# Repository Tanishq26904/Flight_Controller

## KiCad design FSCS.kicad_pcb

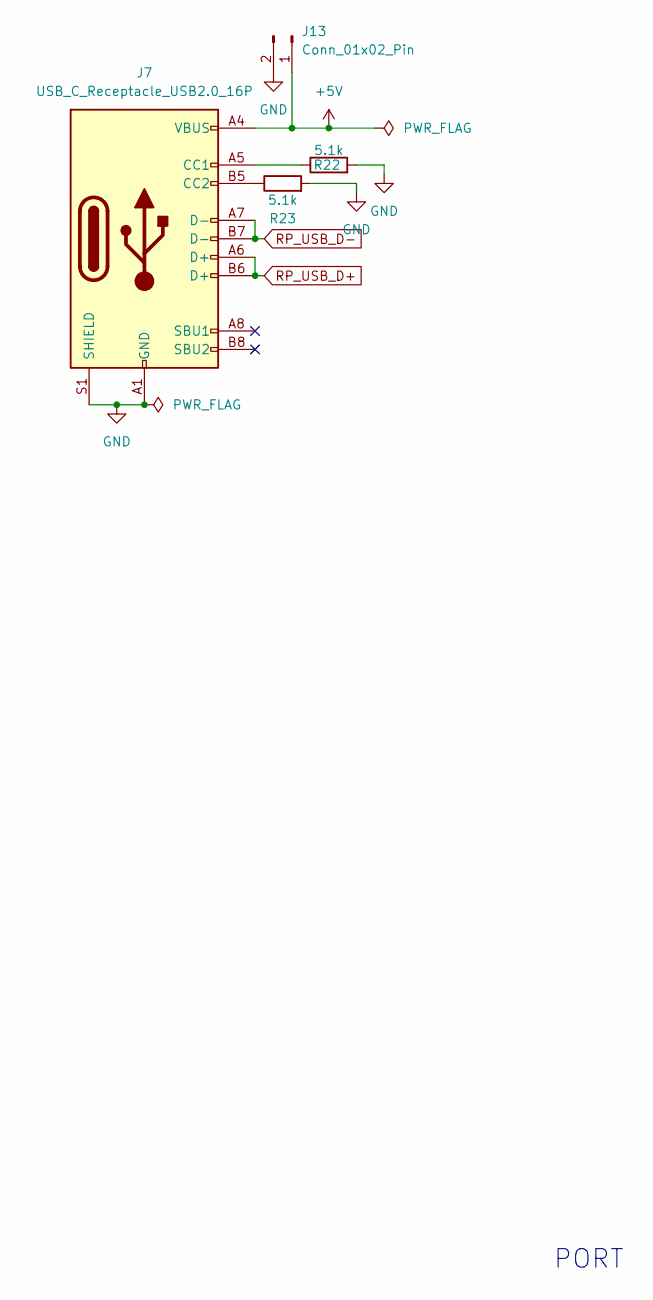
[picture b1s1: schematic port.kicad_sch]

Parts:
J7: USB_C_Receptacle_USB2.0_16P; USB_C_Receptacle_G-Switch_GT-USB-7010ASV
J13: Conn_01x02_Pin; PinHeader_1x02_P2.54mm_Horizontal
R22, R23: 5.1k; R_0603_1608Metric_Pad0.98x0.95mm_HandSolder

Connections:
+5V: J7.A4 (VBUS), J7.A9 (VBUS), J7.B4 (VBUS), J7.B9 (VBUS), J13.1; also elsewhere on the board
GND: J7.A1 (GND), J7.A12 (GND), J7.B1 (GND), J7.B12 (GND), J7.S1 (SHIELD), J13.2, R22.2, R23.2; also elsewhere on the board
unnamed: J7.A5 (CC1), R22.1
unnamed: J7.B5 (CC2), R23.1
RP_USB_D+: J7.A6 (D+), J7.B6 (D+); also elsewhere on the board
RP_USB_D-: J7.A7 (D-), J7.B7 (D-); also elsewhere on the board

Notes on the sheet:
PORT

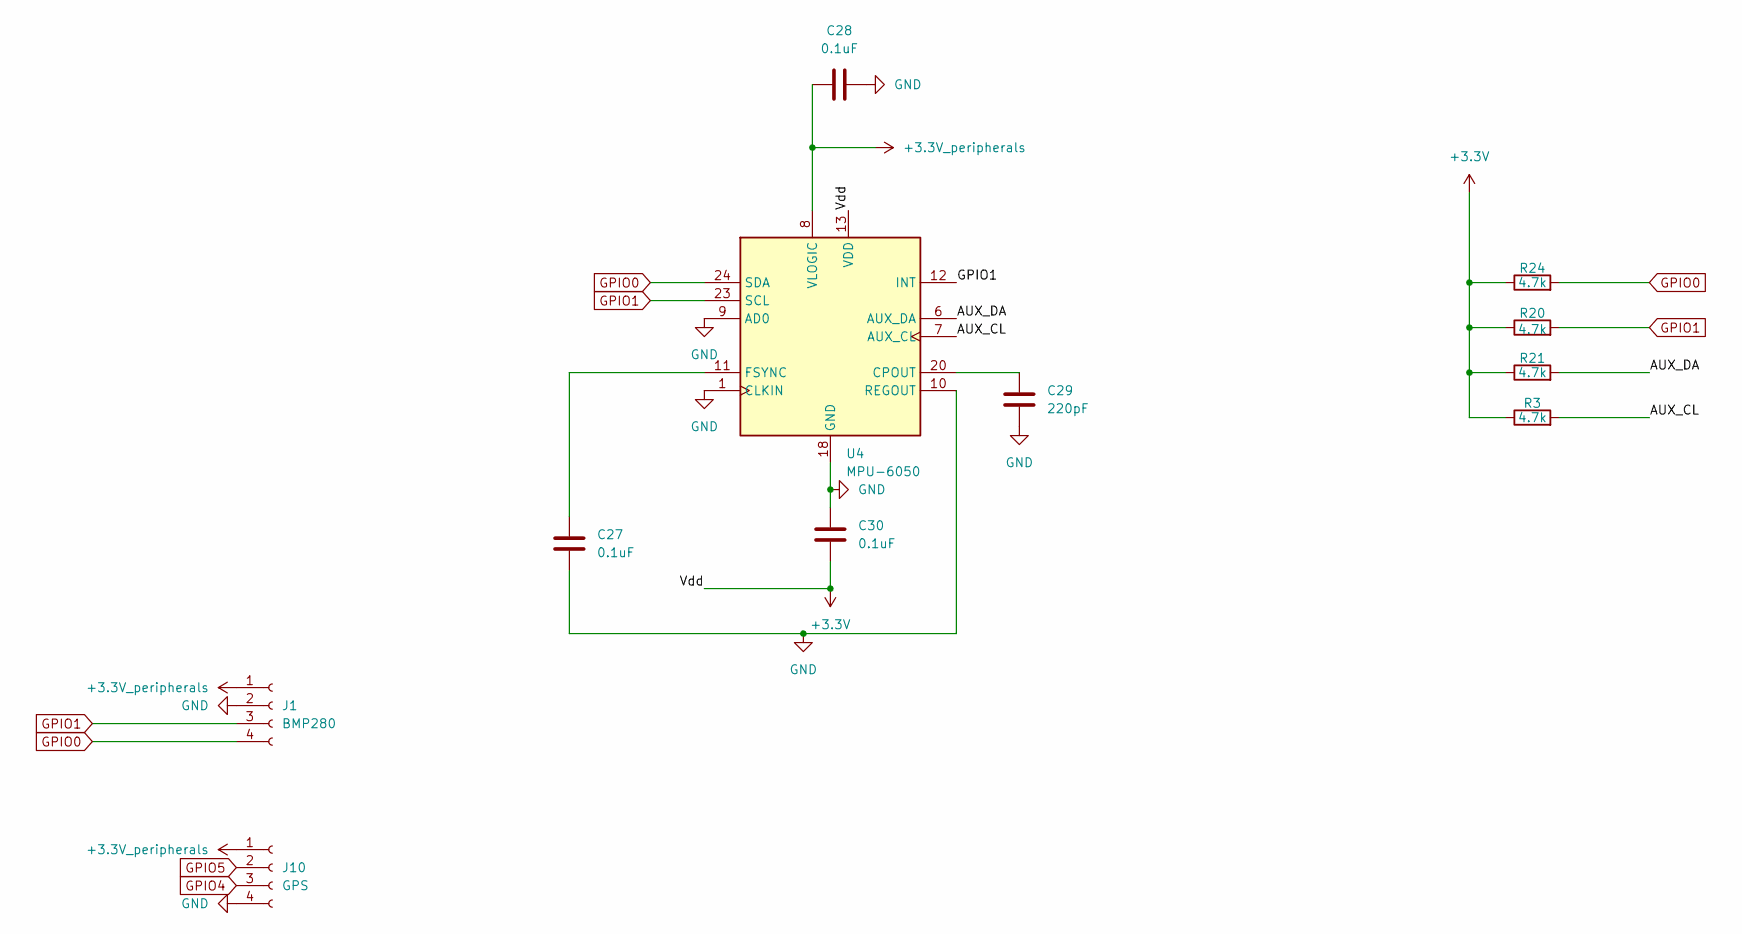
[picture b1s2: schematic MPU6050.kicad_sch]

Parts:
C27, C28, C30: 0.1uF; C_0603_1608Metric_Pad1.08x0.95mm_HandSolder
C29: 220pF; C_0603_1608Metric_Pad1.08x0.95mm_HandSolder
J1: BMP280; PinSocket_1x04_P2.54mm_Vertical
J10: GPS; PinSocket_1x04_P2.54mm_Vertical
R3, R20, R21, R24: 4.7k; R_0603_1608Metric_Pad0.98x0.95mm_HandSolder
U4: MPU-6050; InvenSense_QFN-24_4x4mm_P0.5mm

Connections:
/MPU6050/AUX_CL: R3.2, U4.7 (AUX_CL)
/MPU6050/AUX_DA: R21.2, U4.6 (AUX_DA)
GND: C27.2, C28.2, C29.2, C30.1, J1.2, J10.4, U4.1 (CLKIN), U4.9 (AD0), U4.10 (REGOUT), U4.18 (GND); also elsewhere on the board
GPIO0: J1.4, R24.2, U4.24 (SDA); also elsewhere on the board
GPIO1: J1.3, R20.2, U4.12 (INT), U4.23 (SCL); also elsewhere on the board
GPIO4: J10.3; also elsewhere on the board
GPIO5: J10.2; also elsewhere on the board
unnamed: C29.1, U4.20 (CPOUT)
unnamed: C27.1, U4.11 (FSYNC)

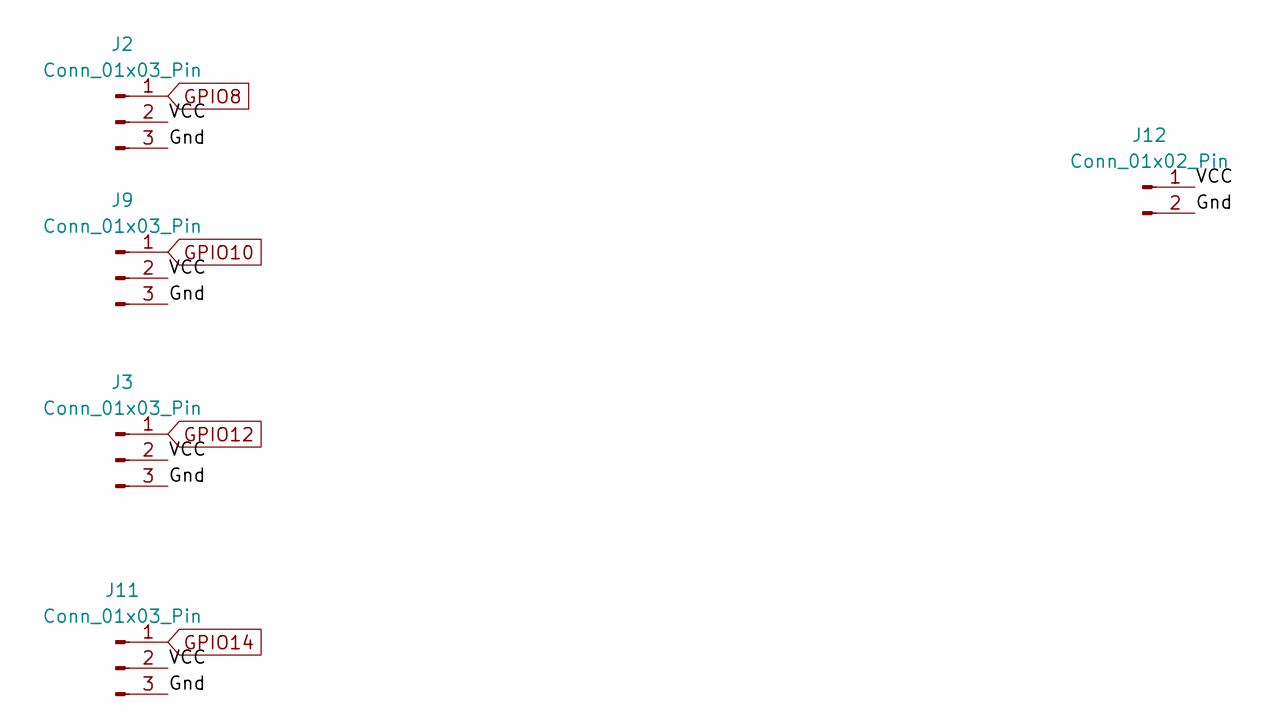
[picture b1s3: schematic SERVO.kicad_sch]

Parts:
J2, J3, J9, J11: Conn_01x03_Pin; PinHeader_1x03_P2.54mm_Vertical
J12: Conn_01x02_Pin; PinHeader_1x02_P2.54mm_Horizontal

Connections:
/SERVO/Gnd: J2.3, J3.3, J9.3, J11.3, J12.2
/SERVO/VCC: J2.2, J3.2, J9.2, J11.2, J12.1
GPIO8: J2.1; also elsewhere on the board
GPIO10: J9.1; also elsewhere on the board
GPIO12: J3.1; also elsewhere on the board
GPIO14: J11.1; also elsewhere on the board

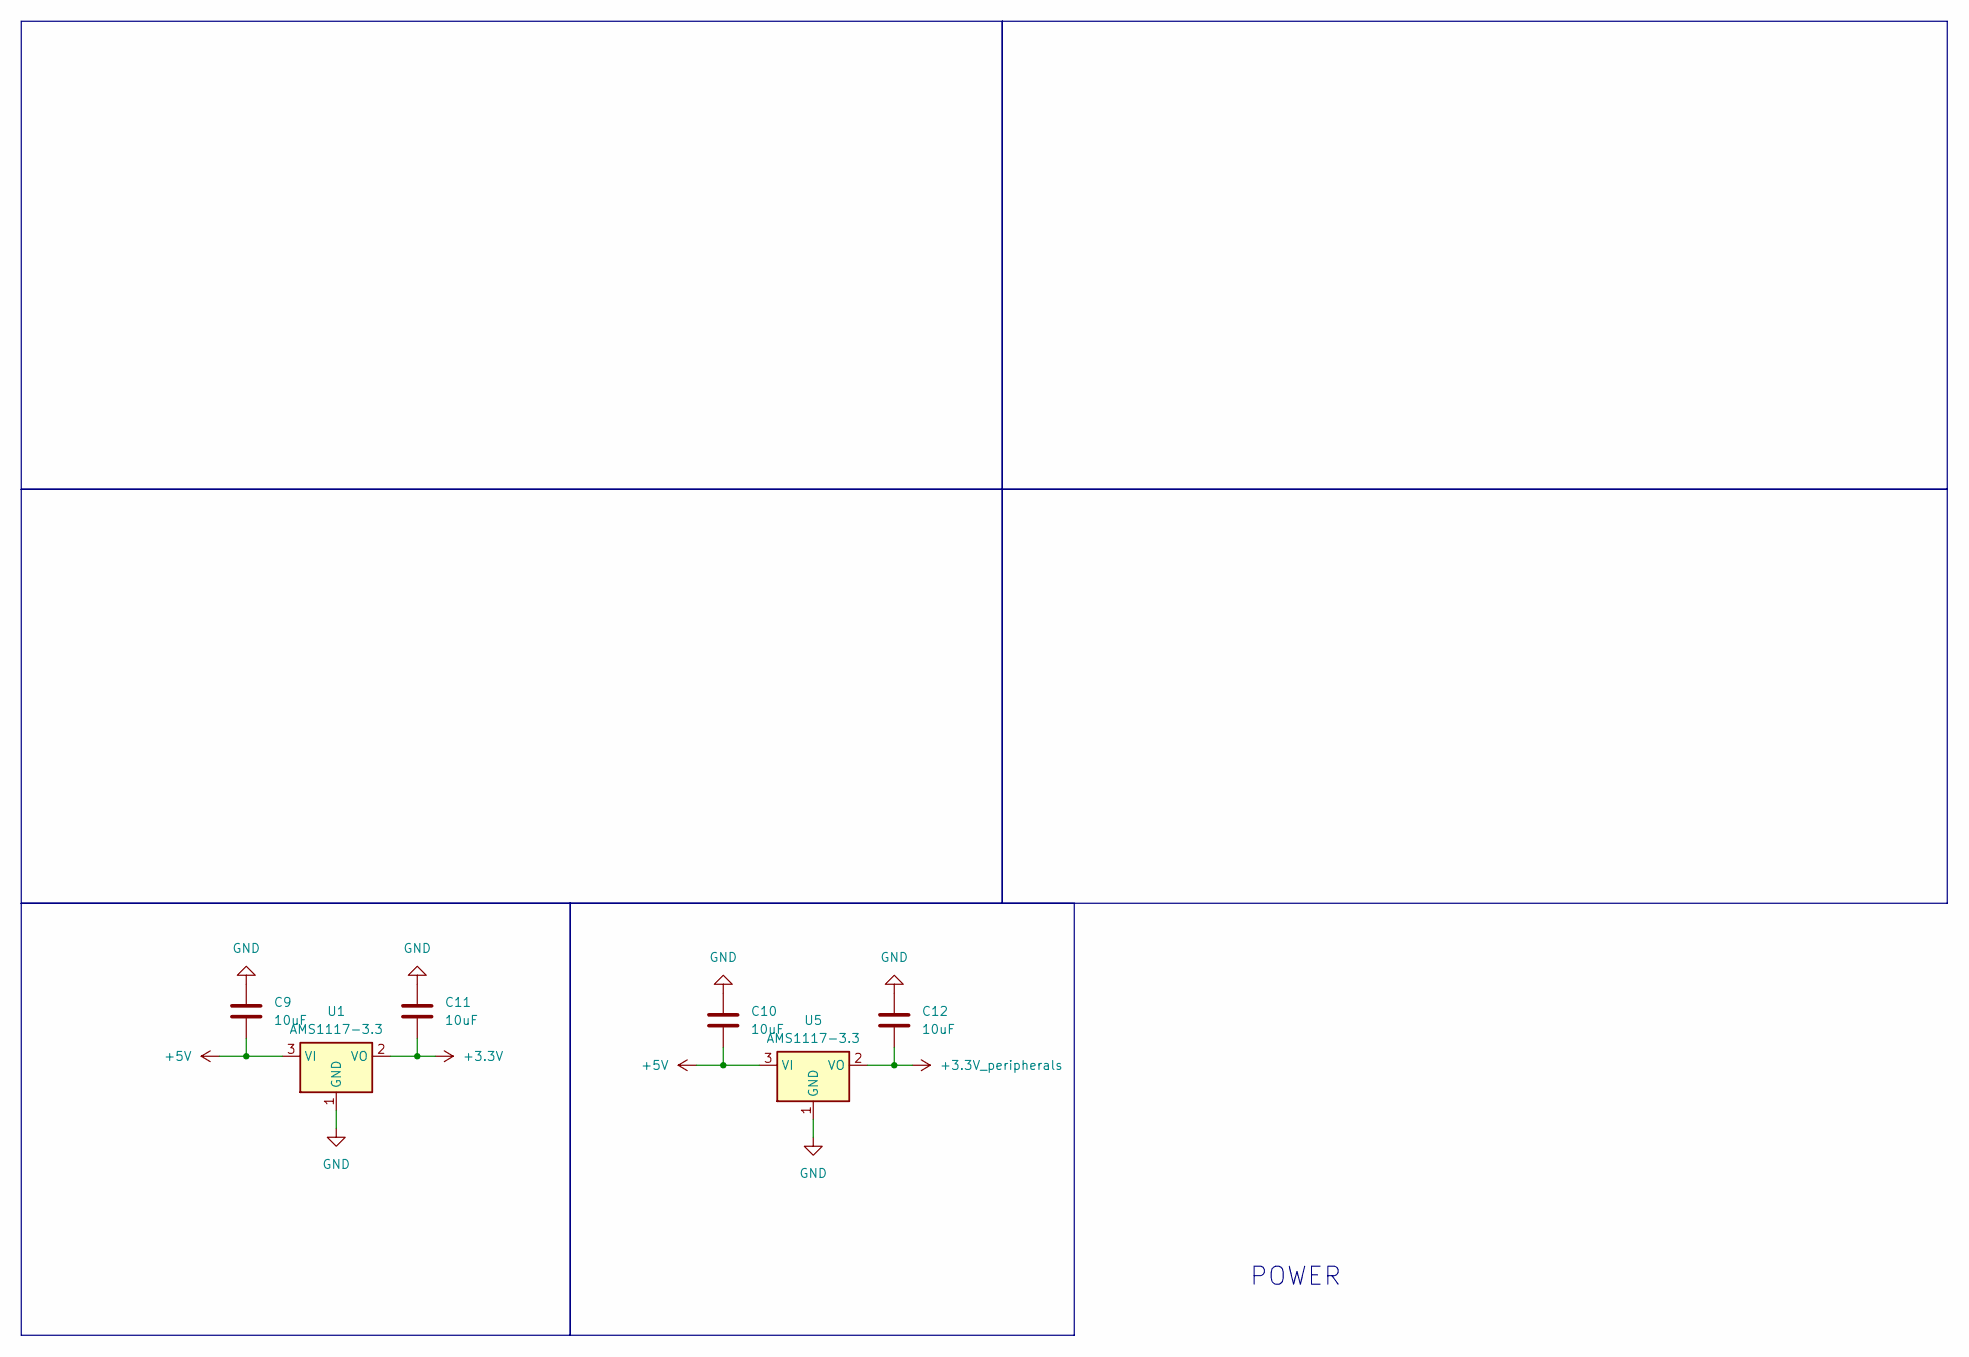
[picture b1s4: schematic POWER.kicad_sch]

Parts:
C9, C10, C11, C12: 10uF; C_0603_1608Metric_Pad1.08x0.95mm_HandSolder
U1, U5: AMS1117-3.3; SOT-223-3_TabPin2

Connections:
+5V: C9.2, C10.2, U1.3 (VI), U5.3 (VI); also elsewhere on the board
GND: C9.1, C10.1, C11.1, C12.1, U1.1 (GND), U5.1 (GND); also elsewhere on the board
unnamed: C12.2, U5.2 (VO)

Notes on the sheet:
POWER

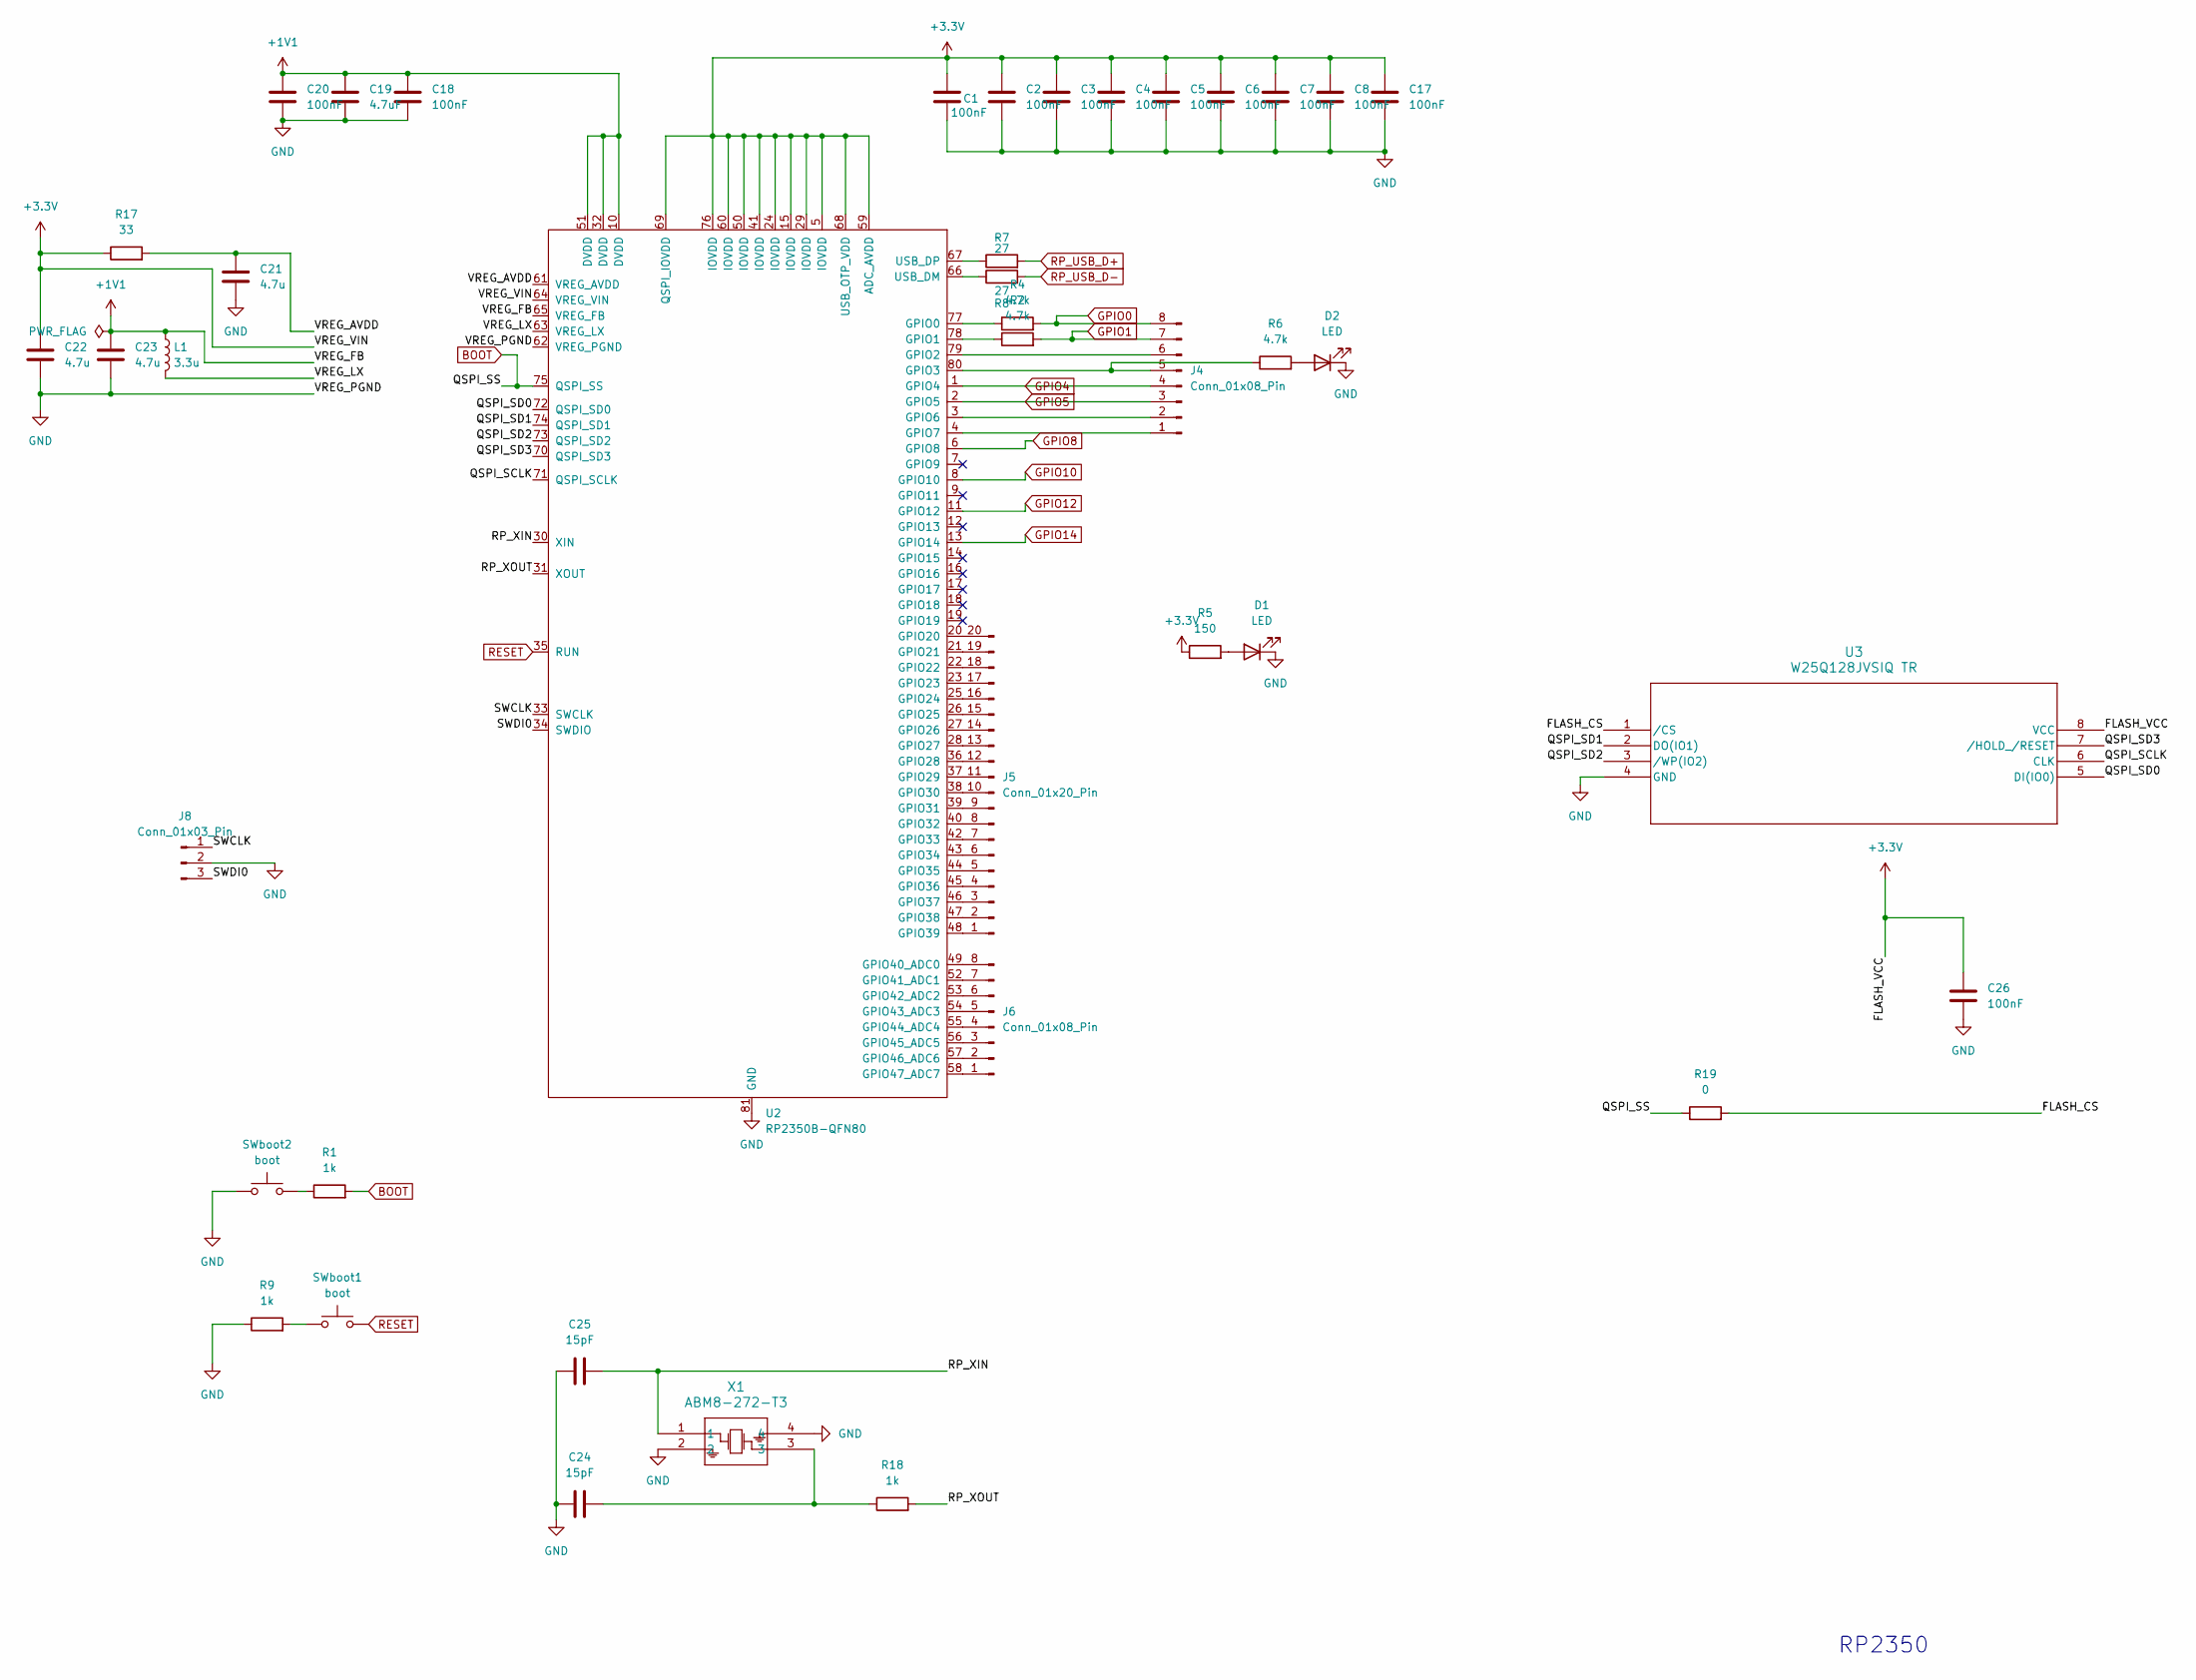
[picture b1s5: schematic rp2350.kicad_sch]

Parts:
C1, C2, C3, C4, C5, C6, C7, C8, C17, C18, C20, C26: 100nF; C_0603_1608Metric_Pad1.08x0.95mm_HandSolder
C19: 4.7uF; C_0603_1608Metric_Pad1.08x0.95mm_HandSolder
C21, C22, C23: 4.7u; C_0603_1608Metric_Pad1.08x0.95mm_HandSolder
C24, C25: 15pF; C_0603_1608Metric_Pad1.08x0.95mm_HandSolder
D1, D2: LED; LED_1206_3216Metric_Pad1.42x1.75mm_HandSolder
J4, J6: Conn_01x08_Pin; PinHeader_1x08_P2.54mm_Vertical
J5: Conn_01x20_Pin; PinHeader_1x20_P2.54mm_Vertical
J8: Conn_01x03_Pin; PinHeader_1x03_P2.54mm_Vertical
L1: 3.3u; L_1210_3225Metric_Pad1.42x2.65mm_HandSolder
R1, R9, R18: 1k; R_0603_1608Metric_Pad0.98x0.95mm_HandSolder
R2, R4, R6: 4.7k; R_0603_1608Metric_Pad0.98x0.95mm_HandSolder
R5: 150; R_0603_1608Metric_Pad0.98x0.95mm_HandSolder
R7, R8: 27; R_0603_1608Metric_Pad0.98x0.95mm_HandSolder
R17: 33; R_0603_1608Metric_Pad0.98x0.95mm_HandSolder
R19: 0; R_0603_1608Metric_Pad0.98x0.95mm_HandSolder
SWboot1, SWboot2: boot; SW_SPST_TL3342
U2: RP2350B-QFN80; QFN-80-1EP_10x10mm_P0.4mm_EP3.4x3.4mm
U3: W25Q128JVSIQ TR; SOIC_208MIL_WIN
X1: ABM8-272-T3; ABM8-272-T3_ABR

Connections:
+1V1: C18.1, C19.1, C20.1, C23.1, L1.1, U2.10 (DVDD), U2.32 (DVDD), U2.51 (DVDD), U2.65 (VREG_FB)
/rp2350/FLASH_CS: R19.2, U3.1 (/CS)
/rp2350/QSPI_SCLK: U2.71 (QSPI_SCLK), U3.6 (CLK)
/rp2350/QSPI_SD0: U2.72 (QSPI_SD0), U3.5 (DI(IO0))
/rp2350/QSPI_SD1: U2.74 (QSPI_SD1), U3.2 (DO(IO1))
/rp2350/QSPI_SD2: U2.73 (QSPI_SD2), U3.3 (/WP(IO2))
/rp2350/QSPI_SD3: U2.70 (QSPI_SD3), U3.7 (/HOLD_/RESET)
/rp2350/RP_XIN: C25.2, U2.30 (XIN), X1.1
/rp2350/RP_XOUT: R18.2, U2.31 (XOUT)
/rp2350/SWCLK: J8.1, U2.33 (SWCLK)
/rp2350/SWDI0: J8.3, U2.34 (SWDIO)
/rp2350/VREG_AVDD: C21.1, R17.2, U2.61 (VREG_AVDD)
/rp2350/VREG_LX: L1.2, U2.63 (VREG_LX)
BOOT: R1.2, R19.1, U2.75 (QSPI_SS)
GND: C1.2, C2.2, C3.2, C4.2, C5.2, C6.2, C7.2, C8.2, C17.2, C18.2, C19.2, C20.2, C21.2, C22.2, C23.2, C24.1, C25.1, C26.2, D1.1 (K), D2.1 (K), J8.2, R9.1, SWboot2.1, U2.62 (VREG_PGND), U2.81 (GND), U3.4 (GND), X1.2, X1.4; also elsewhere on the board
GPIO0: J4.8, R4.2; also elsewhere on the board
GPIO1: J4.7, R2.2; also elsewhere on the board
GPIO4: J4.4, U2.1 (GPIO4); also elsewhere on the board
GPIO5: J4.3, U2.2 (GPIO5); also elsewhere on the board
GPIO8: U2.6 (GPIO8); also elsewhere on the board
GPIO10: U2.8 (GPIO10); also elsewhere on the board
GPIO12: U2.11 (GPIO12); also elsewhere on the board
GPIO14: U2.13 (GPIO14); also elsewhere on the board
unnamed: C24.2, R18.1, X1.3
unnamed: D1.2 (A), R5.2
unnamed: D2.2 (A), R6.2
unnamed: J4.1, U2.4 (GPIO7)
unnamed: J4.2, U2.3 (GPIO6)
unnamed: J4.5, R6.1, U2.80 (GPIO3)
unnamed: J4.6, U2.79 (GPIO2)
unnamed: J5.1, U2.48 (GPIO39)
unnamed: J5.2, U2.47 (GPIO38)
unnamed: J5.3, U2.46 (GPIO37)
unnamed: J5.4, U2.45 (GPIO36)
unnamed: J5.5, U2.44 (GPIO35)
unnamed: J5.6, U2.43 (GPIO34)
unnamed: J5.7, U2.42 (GPIO33)
unnamed: J5.8, U2.40 (GPIO32)
unnamed: J5.9, U2.39 (GPIO31)
unnamed: J5.10, U2.38 (GPIO30)
unnamed: J5.11, U2.37 (GPIO29)
unnamed: J5.12, U2.36 (GPIO28)
unnamed: J5.13, U2.28 (GPIO27)
unnamed: J5.14, U2.27 (GPIO26)
unnamed: J5.15, U2.26 (GPIO25)
unnamed: J5.16, U2.25 (GPIO24)
unnamed: J5.17, U2.23 (GPIO23)
unnamed: J5.18, U2.22 (GPIO22)
unnamed: J5.19, U2.21 (GPIO21)
unnamed: J5.20, U2.20 (GPIO20)
unnamed: J6.1, U2.58 (GPIO47_ADC7)
unnamed: J6.2, U2.57 (GPIO46_ADC6)
unnamed: J6.3, U2.56 (GPIO45_ADC5)
unnamed: J6.4, U2.55 (GPIO44_ADC4)
unnamed: J6.5, U2.54 (GPIO43_ADC3)
unnamed: J6.6, U2.53 (GPIO42_ADC2)
unnamed: J6.7, U2.52 (GPIO41_ADC1)
unnamed: J6.8, U2.49 (GPIO40_ADC0)
unnamed: R1.1, SWboot2.2
unnamed: R9.2, SWboot1.1
unnamed: R4.1, U2.77 (GPIO0)
unnamed: R2.1, U2.78 (GPIO1)
unnamed: R8.1, U2.66 (USB_DM)
unnamed: R7.1, U2.67 (USB_DP)
RESET: SWboot1.2, U2.35 (RUN)
RP_USB_D+: R7.2; also elsewhere on the board
RP_USB_D-: R8.2; also elsewhere on the board

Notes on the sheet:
RP2350

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
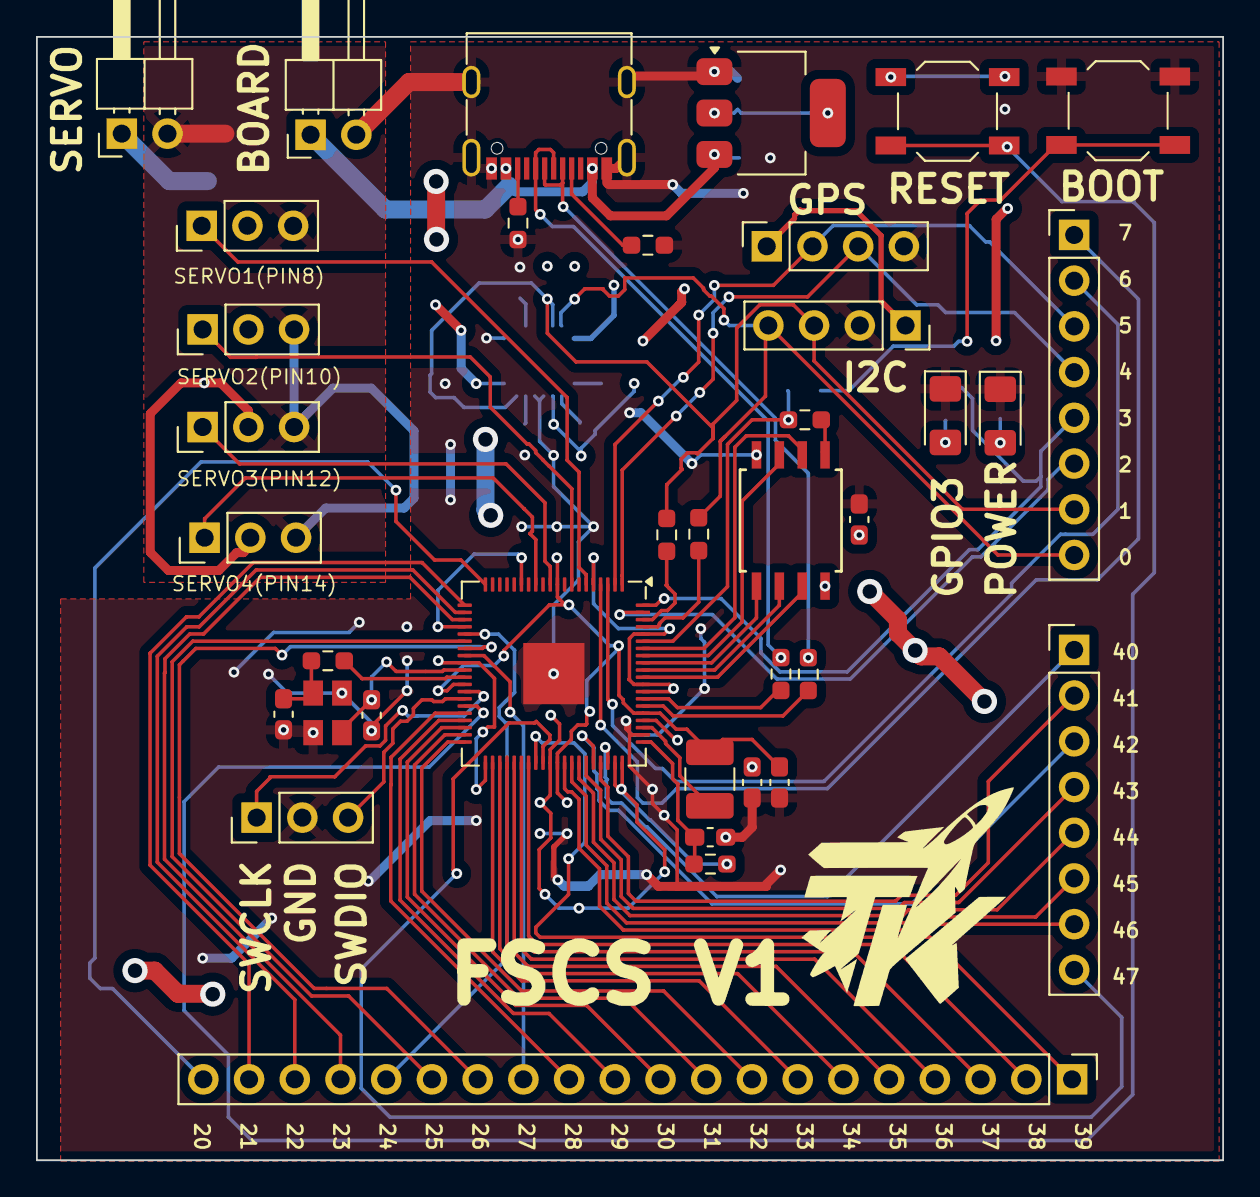
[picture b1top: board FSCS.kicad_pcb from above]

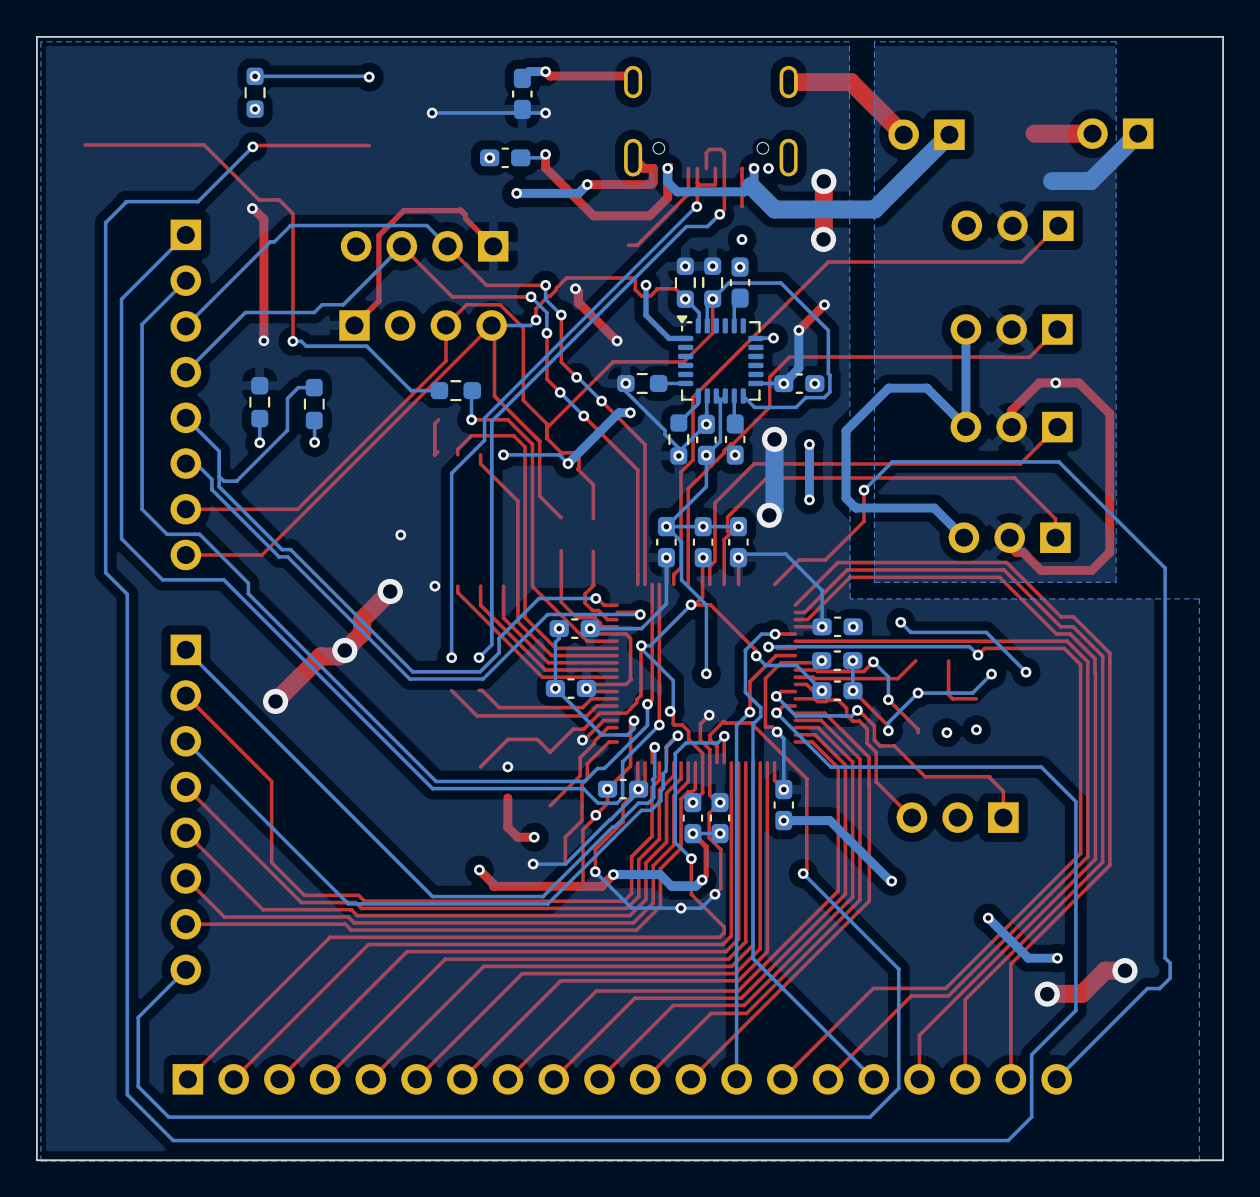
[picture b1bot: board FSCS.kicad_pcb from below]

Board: 2 copper layers, 65.9 x 62.4 mm, 64 parts (27 on the bottom side), 77 nets.

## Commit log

2025-12-19 Initial KiCad project
2025-12-19 Update all project files
2025-12-19 Update plot files
2025-12-19 plot file colour
2026-01-18 schematic
